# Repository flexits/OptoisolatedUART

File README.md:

# OptoisolatedUART
Простейшая опторазвязка интерфейса UART

Проект в KiCAD 6

Для разных оптопар может потребоваться пересчитать номиналы токоограничительных резисторов.
С укзаанными номиналами самая быстрая из проверенных оптопар - SFH617A. Не успевает на 115200 бод, но сорее всего нормально заработает на 9600 и ниже.

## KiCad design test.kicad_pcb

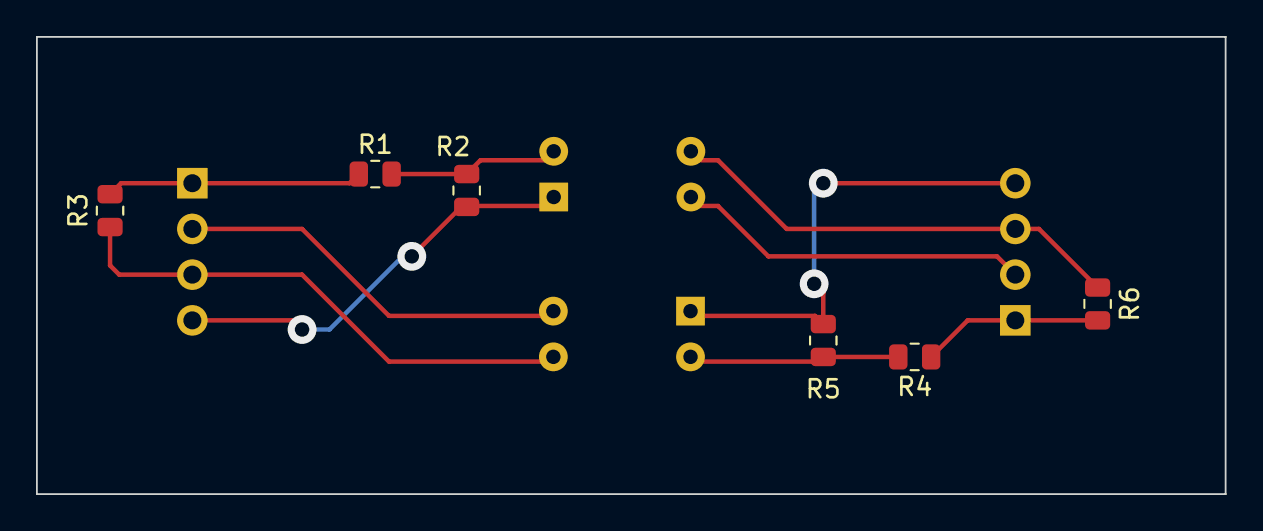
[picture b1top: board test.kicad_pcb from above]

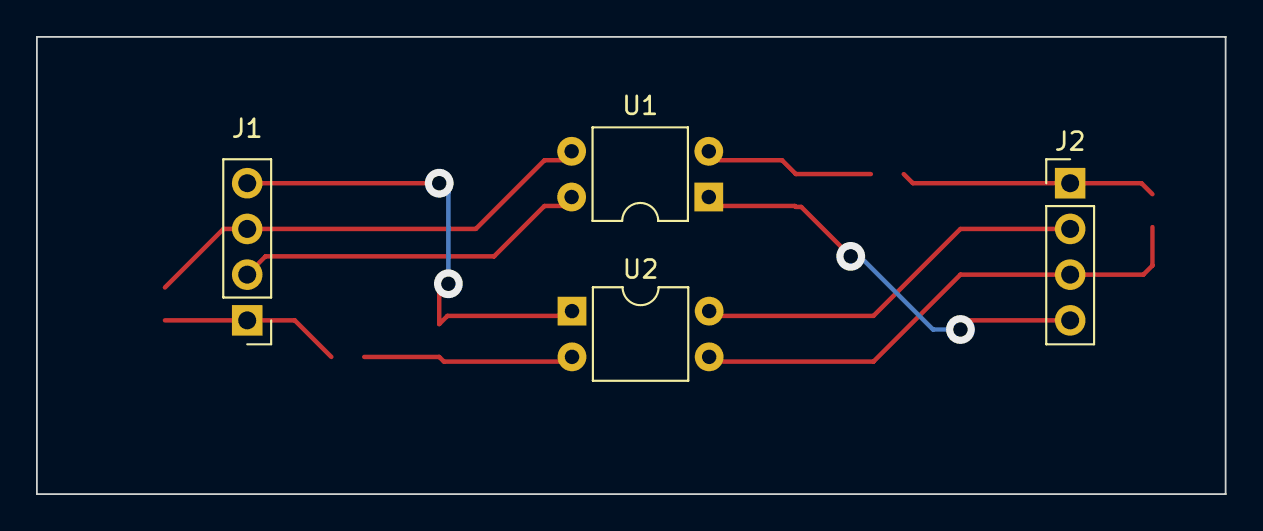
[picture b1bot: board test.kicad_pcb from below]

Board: 2 copper layers, 66.0 x 25.4 mm, 10 parts (4 on the bottom side), 10 nets.

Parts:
J1, J2: Conn_01x04; PinHeader_1x04_P2.54mm_Vertical
R1, R4: 510R; R_0805_2012Metric
R2, R5: 10k; R_0805_2012Metric
R3, R6: 2k2; R_0805_2012Metric
U1, U2: SFH618A; DIP-4_W7.62mm

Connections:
+5V: J2.1, R1.1, R3.2
GNDS: J2.2, U2.3
unnamed: J1.1, R4.1, R6.2
unnamed: J1.2, U1.3
unnamed: J1.3, R6.1, U1.4
unnamed: J1.4, R5.2, U2.1, U2.2
unnamed: R1.2, R2.1
unnamed: J2.4, R2.2, U1.1, U1.2
unnamed: J2.3, R3.1, U2.4
unnamed: R4.2, R5.1
